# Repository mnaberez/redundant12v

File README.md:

# Rackmount Redundant 12V Power Supply

This is a redundant, but not hot-swappable, 12VDC power supply.  It has these features:

 - Two AC cords.  Either cord can lose AC power without disrupting the 12VDC output.

 - Five 12VDC output jacks.  Any individual jack can supply ~6A maximum but the supply is only capable of providing ~16A maximum across all jacks.

 - Remote monitoring.  A serial port provides a simple "on/off" status that indicates when one of the two onboard DC supplies loses its AC power or otherwise fails.

It is built on a 1U rack shelf but requires at least 2U because it is slightly taller than 1U.  The extra air space is also needed for cooling because the supply has no fans.

## Background

Rackmount [Automatic Transfer Switches](https://web.archive.org/web/20220408134749/https://www.youtube.com/watch?v=JSWmmY9tKrM) from companies such as [APC](https://web.archive.org/web/20220408135631if_/https://download.schneider-electric.com/files?p_File_Name=BSTY-AQNP38_R0_EN.pdf&p_Doc_Ref=SPD_BSTY-AQNP38_EN&p_enDocType=Catalog) and [CyberPower](https://web.archive.org/web/20220408140138if_/https://www.cyberpower.com/tw/en/File/GetCyberpowerFileByDocId/DS-21040002-01) can be used to provide AC power redundancy for devices with a single AC cord.  I wanted redundant power for the single-corded devices in my rack and noticed that they all ran off 12VDC power bricks.  Instead of buying an ATS unit and plugging the bricks into it, I built this redundant 12VDC supply to eliminate the bricks.  It can be built for less than the cost of most ATS units.

## Parts List

| Part | Qty | Notes |
|------|-----|-------|
|[Meanwell ERDN40-12 12VDC Redundancy Module](https://www.mouser.com/ProductDetail/709-ERDN40-12) | 1 | [Datasheet](https://web.archive.org/web/20220407021145if_/https://www.meanwell.com/upload/pdf/ERDN40/ERDN40-spec.pdf) |
|[Meanwell MSP-200-12 12VDC 16.7A Power Supply](https://www.mouser.com/ProductDetail/709-MSP200-12) | 2 | [Datasheet](https://web.archive.org/web/20220407021309if_/https://www.mouser.com/datasheet/2/260/MSP_200_SPEC-1109886.pdf).  Selected for built-in protections and no required minimum current. |
|[Pinfox 10' 18 AWG 3 Prong Heavy Duty 120V 10A AC Cord](https://www.amazon.com/gp/product/B07QYRMD6D) | 2 | One AC cord for each MSP-200-12. |
|[Raising Electronics 701401004 19" 1U 12" Deep Rack Shelf](https://www.amazon.com/gp/product/B01M8HKRA7) | 1 | [Product Page](https://web.archive.org/web/20220408132026if_/https://risingracks.com/cantilever-server-shelf-vented-black-shelves-rack-mount-19-1u-12-300mm-deep/) |
|[10pc M3x6mm Plastic Pan Head Screw](https://www.ebay.com/itm/254913074827) | 1 | 10 screws used for mounting the Meanwell units to the shelf.  Plastic ensures no possibility of shorting. |
|[10pc M3x25mm Female-Female Steel Standoff](https://www.ebay.com/itm/113410581076) | 1 | 4 standoffs used inside the project box to mount it to the shelf and secure the lid |
|[25pc M3x8mm Pan Head Screw Steel Black](https://www.ebay.com/itm/111839544046) | 1 | 8 screws used with the 4 project box standoffs (2 screws per standoff) |
|[50pcs M3x6mm Nylon Standoffs with M3x6mm Nylon Screws](https://www.ebay.com/itm/262850128455) | 1 | 4 standoffs and 4 screws used to mount PCB inside project box.  Plastic ensures no possibility of shorting.  Standoffs are epoxied to the project box. |
|[Hammond 1591HSBK Project Box](https://www.digikey.com/en/products/detail/hammond-manufacturing/1591HSBK/130882) | 1 | [Datasheet](https://web.archive.org/web/20210928162934if_/http://www.hammondmfg.com/pdf/1591H.pdf), [Bulletin](https://web.archive.org/web/20220407164638if_/https://www.mouser.com/datasheet/2/177/1591-1389824.pdf) |
|[L-Com SDG400XS D-Sub 50pc Jackscrew/Washer/Nut](https://www.newark.com/l-com/sdg400xs/jack-screw-4-40-10-16mm/dp/63K2685) | 1 | [Datasheet](https://web.archive.org/web/20220827230745if_/https://www.l-com.com/Images/Downloadables/2D/SDG450XS_2D.pdf).  2 jackscrews, 2 lock washers, and 2 hex nuts used to mount DB9 to project box. |
|[5pcs DB9 Female to IDC Panel Mount](https://www.ebay.com/itm/311374355272) | 1 | 1 DB9 connector used to make the DB9-to-PCB cable inside the project box. |
|[10pcs 2x5 pin IDC Female](https://www.ebay.com/itm/323745402692) | 1 | 1 IDC connector used to make the DB9-to-PCB cable inside the project box.  The top of the strain relief must be shaved down a bit to fit in the box. |
|[Ribbon Cable 14 conductor 6' long](https://www.ebay.com/itm/282211468932) | 1 | Cut down to 10 conductors and 6" long, used to make the DB9-to-PCB cable inside the project box. |
|[DB9 Male/Female 5' Cable](https://www.mouser.com/ProductDetail/523-CS-DSDMDB09MF005) | 1 | [Datasheet](https://web.archive.org/web/20220719155819if_/https://www.mouser.com/datasheet/2/18/1/CS_DSDMDB09MF-2079775.pdf).  For direct connection between the box and a PC with a DB9 serial port. |
|[FTDI-US232R-100 1m USB-Serial Cable](https://www.mouser.com/ProductDetail/895-US232R-100-BLK) | 1 | [Datasheet](https://web.archive.org/web/20220828230546if_/https://www.mouser.com/datasheet/2/163/DS_US232R-10_R-100-500-1669828.pdf).  For connecting to a PC without a DB9 serial port, use this adapter together with the above DB9 cable. |
|[Lumex SSI-LXH387GD Panel Mount Green LED](https://www.mouser.com/ProductDetail/696-SSI-LXH387GD) | 2 | [Datasheet](https://web.archive.org/web/20221002231549if_/https://www.mouser.com/datasheet/2/244/LUMX_S_A0001762456_1-2551886.pdf).  Mounted on project box to show the "on" status of each power supply.
|[Switchcraft L712ASH 2.5mm Locking Barrel Socket](https://www.mouser.com/ProductDetail/502-L712ASH) | 5 | [Datasheet](https://web.archive.org/web/20220407035419if_/https://www.mouser.com/datasheet/2/393/L712ASH-L722ASH_CD-1110860.pdf), [Bulletin](https://web.archive.org/web/20220407164041if_/https://www.switchcraft.com/Documents/switchcraft_npb_637_high_temp_jacks_plugs.pdf).  Mounted on project box for DC outputs. |
|[Switchcraft 761KSH15 2.5mm Locking Barrel Plug](https://www.mouser.com/ProductDetail/502-761KSH15) | 5 | [Datasheet](https://web.archive.org/web/20220407035117if_/https://www.mouser.com/datasheet/2/393/761KSH-S761KSH_CD-1110850.pdf). See bulletin above for electrical info.  For building DC cables out to devices. |
|[14 AWG GXL Wire 10' Long](https://www.ebay.com/itm/293094627307) | 3 | 1 each: red, green, black.  Cut to length for high current DC wiring |
|[1200Pcs Assorted Crimp Terminals](https://www.ebay.com/itm/172856488315) | 1 | 21 M4 size ring connectors used with terminal blocks on Meanwell units |
|[DC Extension Cable 18 AWG 12VDC 10A 33' Long](https://www.ebay.com/itm/133233779533) | 1 | Connectors cut off and discarded; used to make output cables and for wiring inside Project Box |
|[10pc Dupont 2x2 Female Housing](https://www.ebay.com/itm/141510327734) | 1 | 1 housing used to make ERDN40 alarm cable |
|[10pc Dupont 2-pin 26AWG Female-Female Jumper Cable](https://www.ebay.com/itm/254959908608) | 1 | 2 cables used to make ERDN40 alarm cable |
|[Molex KK 22-01-3077 7-pin Housing](https://www.mouser.com/ProductDetail/538-22-01-3077)| 1 | 1 housing used for PCB connector |
|[125pc Rubber Grommet Set](https://www.ebay.com/itm/221291687081) | 1 | 1 grommet used around wiring from ERDN40 into project box |
|[TICONN 80pc Stainless Steel Hose Clamp Set](https://www.amazon.com/gp/product/B094YP2F3D) | 1 | 3 hose clamps used for AC cord strain relief |
|[100pc 1/4" Aluminum Pop Rivet Set](https://www.harborfreight.com/100-piece-1-4-quarter-inch-aluminum-blind-rivet-set-67619.html) | 1 | 3 pop rivets used to secure hose clamps to shelf |
|[6pc Phoenix Contact Cable Tie Mount Base](https://www.mouser.com/ProductDetail/651-3240709) | 1 | 3 bases used for cable management |
|[Panduit Cable Tie Assortment](https://www.mouser.com/ProductDetail/644-KB-550) | 1 | 3 ties used for cable management |
|[42pc Marine Heat Shrink Tubing](https://www.harborfreight.com/42-piece-marine-heat-shrink-tubing-67598.html) | 1 | For insulating cable ends and also cable management |

## PCB Components

| Part | Qty | Reference Designators |
|------|-----|-----------------------|
|[ATTINY212-SSF](https://www.mouser.com/ProductDetail/579-ATTINY212-SSF) Microcontroller SOIC-8 | 1 | U1 |
|[MAX232EID](https://www.mouser.com/ProductDetail/595-MAX232EID) TI RS232 Transceiver SOIC-8 | 1 | U2 |
|[ECS-3951M-018-AU-TR](https://www.mouser.com/ProductDetail/520-3951M-018-AU) Oscillator 1.8432 MHz | 1 | X1 |
|[BZX84-A15,215](https://www.mouser.com/ProductDetail/771-BZX84-A15,215) Zener Diode 15V | 1 | D1 |
|[F1206B1R00FSTR](https://www.mouser.com/ProductDetail/581-F1206B1R00FSTR) Fuse 1206 | 1 | F1 |
|[08055C104J4T2A](https://www.mouser.com/ProductDetail/581-08055C104J4T2A) Capacitor 0.1uF 50V 0805 | 4 | C1, C2, C4, C8 |
|[08053C105K4Z4A](https://www.mouser.com/ProductDetail/581-08053C105K4Z4A) Capacitor 1uF 25V 0805 | 4 | C3, C5, C6, C7 |
|[CGA4J1X7S1E106K125AC](https://www.mouser.com/ProductDetail/810-CGA4J1X7S1E106K1) Capacitor 10uF 25V 0805 | 1 | C9 |
|[RK73H2ARTTD4702F](https://www.mouser.com/ProductDetail/660-RK73H2ARTTD4702F) Resistor 47K 0805 | 2 | R1, R2 |
|[ERJ-P06F2000V](https://www.mouser.com/ProductDetail/667-ERJ-P06F2000V) Resistor 200ohm  0805 | 2 | R3, R4 |
|[22-12-2074](https://www.mouser.com/ProductDetail/538-22-12-2074) Molex KK 7-pin Right Angle | 1 | J1 |
|[IDC 2x5 Header](https://www.ebay.com/itm/254517739367) Shrouded Through Hole | 1 | J2 |

## Author

[Mike Naberezny](https://github.com/mnaberez)

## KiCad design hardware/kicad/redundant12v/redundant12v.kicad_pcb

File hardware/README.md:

# Hardware

The redundant power supply is mostly wired by hand but a printed circuit board with a microcontroller is used to report the status to a PC.  The board was designed using KiCad.  The [schematic](./redundant12v/schematic.pdf) and [Gerber files](./redundant12v/gerbers.zip) are the final version.  See [`firmware/`](../firmware) for how to program the microcontroller.

## Photos

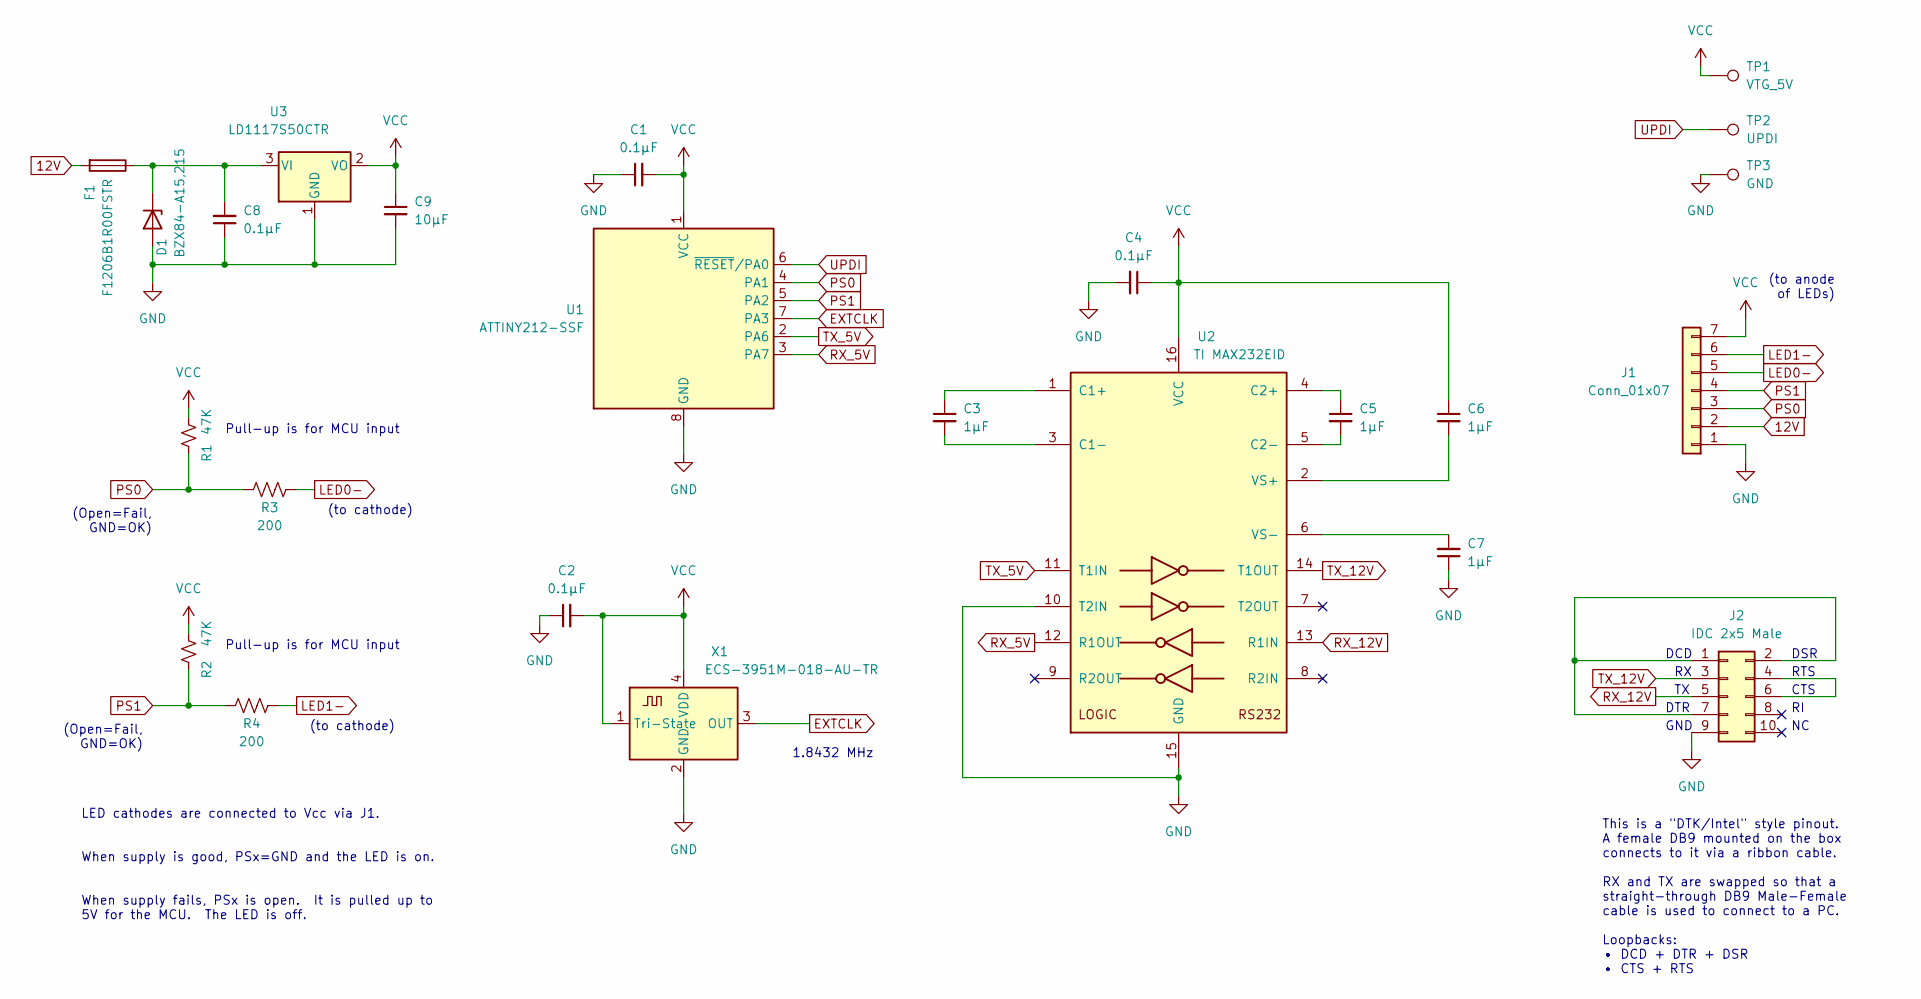
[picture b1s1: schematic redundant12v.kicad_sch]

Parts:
C1, C2, C4, C8: 0.1μF; C_0805_2012Metric_Pad1.18x1.45mm_HandSolder
C3, C5, C6, C7: 1μF; C_0805_2012Metric_Pad1.18x1.45mm_HandSolder
C9: 10μF; C_0805_2012Metric_Pad1.18x1.45mm_HandSolder
D1: BZX84-A15,215; SOT-23
F1: F1206B1R00FSTR; Fuse_1206_3216Metric_Pad1.42x1.75mm_HandSolder
J1: Conn_01x07; Molex_KK-254_AE-6410-07A_1x07_P2.54mm_Vertical
J2: IDC 2x5 Male; IDC-Header_2x05_P2.54mm_Vertical
R1, R2: 47K; R_0805_2012Metric_Pad1.20x1.40mm_HandSolder
R3, R4: 200; R_0805_2012Metric_Pad1.20x1.40mm_HandSolder
TP1: VTG_5V; TestPoint_Pad_D2.5mm
TP2: UPDI; TestPoint_Pad_D2.5mm
TP3: GND; TestPoint_Pad_D2.5mm
U1: ATTINY212-SSF; SOIC-8_3.9x4.9mm_P1.27mm
U2: TI MAX232EID; SOIC-16_3.9x9.9mm_P1.27mm
U3: LD1117S50CTR; SOT-223-3_TabPin2
X1: ECS-3951M-018-AU-TR; Oscillator_SMD_Abracon_ASV-4Pin_7.0x5.1mm_HandSoldering

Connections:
12V: F1.2, J1.2
EXTCLK: U1.7 (PA3), X1.3 (OUT)
GND: C1.1, C2.1, C4.2, C7.1, C8.1, C9.2, D1.1 (A), J1.1, J2.9, TP3.1, U1.8 (GND), U2.10 (T2IN), U2.15 (GND), U3.1 (GND), X1.2 (GND)
LED0-: J1.5, R3.2
LED1-: J1.6, R4.2
unnamed: C3.1, U2.1 (C1+)
unnamed: C3.2, U2.3 (C1-)
unnamed: C5.1, U2.4 (C2+)
unnamed: C5.2, U2.5 (C2-)
unnamed: C6.2, U2.2 (VS+)
unnamed: C7.2, U2.6 (VS-)
unnamed: C8.2, D1.3 (K), F1.1, U3.3 (VI)
unnamed: J2.1, J2.2, J2.7
unnamed: J2.4, J2.6
PS0: J1.3, R1.2, R3.1, U1.4 (PA1)
PS1: J1.4, R2.2, R4.1, U1.5 (PA2)
RX_5V: U1.3 (PA7), U2.12 (R1OUT)
RX_12V: J2.5, U2.13 (R1IN)
TX_5V: U1.2 (PA6), U2.11 (T1IN)
TX_12V: J2.3, U2.14 (T1OUT)
UPDI: TP2.1, U1.6 (~RESET/PA0)
VCC: C1.2, C2.2, C4.1, C6.1, C9.1, J1.7, R1.1, R2.1, TP1.1, U1.1 (VCC), U2.16 (VCC), U3.2 (VO), X1.1 (Tri-State), X1.4 (VDD)

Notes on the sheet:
RTS
1.8432 MHz
DTR
(to anode of LEDs)
DCD
(to cathode)
(Open=Fail, GND=OK)
LED cathodes are connected to Vcc via J1. When supply is good, PSx=GND and the LED is on. When supply fails, PSx is open. It is pulled up to 5V for the MCU. The LED is off.
This is a "DTK/Intel" style pinout. A female DB9 mounted on the box connects to it via a ribbon cable. RX and TX are swapped so that a straight-through DB9 Male-Female cable is used to connect to a PC. Loopbacks: • DCD + DTR + DSR • CTS + RTS
DSR
CTS
Pull-up is for MCU input
GND

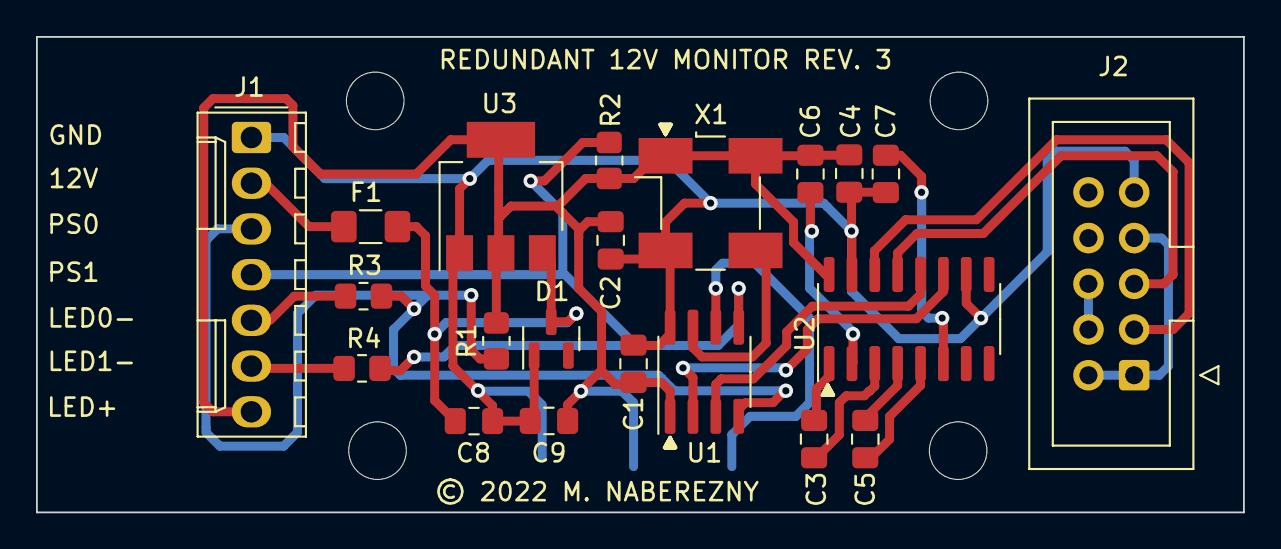
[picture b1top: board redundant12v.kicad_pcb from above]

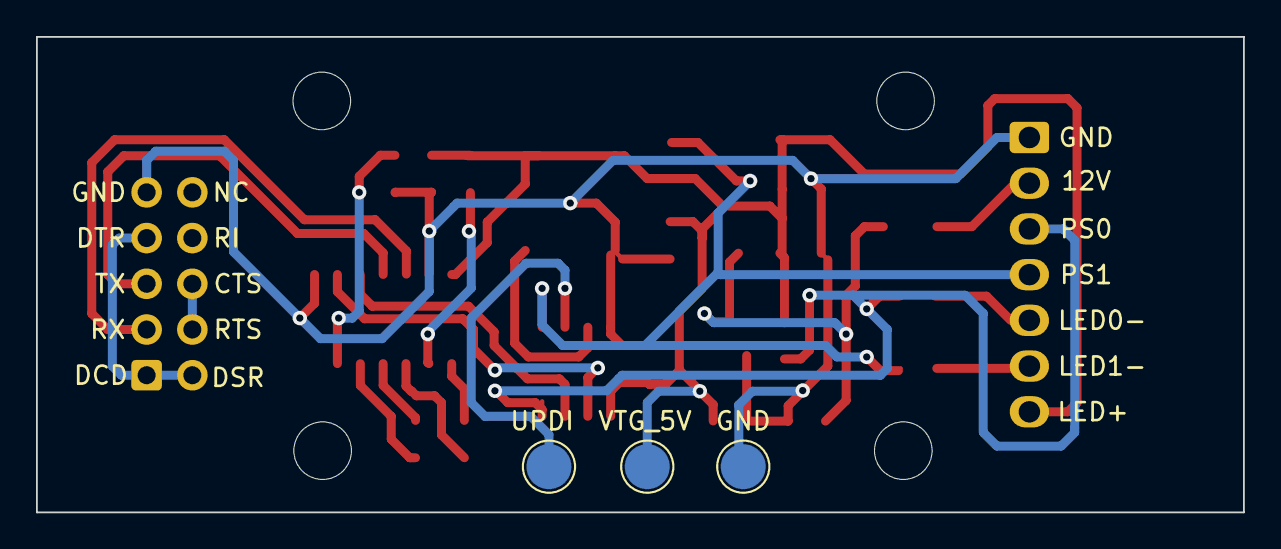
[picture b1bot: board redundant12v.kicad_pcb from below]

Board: 2 copper layers, 67.1 x 26.4 mm, 24 parts (3 on the bottom side), 22 nets.

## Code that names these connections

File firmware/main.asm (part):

;ATtiny212 or ATtiny412
;1 VCC
;2 PA6 TX to MAX232
;3 PA7 RX from MAX232
;4 PA1 Digital Input: Power Supply 0 failed (0=ok, 1=failed)
;5 PA2 Digital Input: Power Supply 1 failed (0=ok, 1=failed)
;6 UPDI
;7 EXTCLK (from 1.8432 MHz oscillator)
;8 GND
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    ldi r18, 25             ;Debounce: PORTA must be the same for N readings

1$: lds r16, PORTA_IN       ;Read once
    andi r16, 0b00000110    ;PA2=Power Supply 1, PA1=Power Supply 0

    push r16
    rcall delay_1ms         ;Delay 1ms
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
;Set up GPIO directions (UART pin directions are set in uart_init)
gpio_init:
    ldi r16, 1<<2 | 1<<1    ;PA2, PA1 = input
    sts PORTA_DIRCLR, r16
    ret

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    sts USART0_CTRLC, r16

    ;Set pin directions
    ldi r16, 1<<7           ;pa7 = rx (input)
    sts PORTA_DIRCLR, r16
    ldi r16, 1<<6           ;pa6 = tx (output)
    sts PORTA_DIRSET, r16

    ;Enable transmit and receive
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
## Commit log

2022-04-08 Initial import
2022-04-10 Add Dupot connectors to parts list
2022-06-28 Add M3 standoffs
2022-06-30 Ignore build artifacts
2022-06-30 Add initial firmware (serial loopback only)
2022-06-30 Add workflow for GitHub Actions
2022-06-30 Add license (BSD 3-clause)
2022-06-30 Add screws used with standoffs
2022-07-04 Send "PS0=OK,PS1=OK\r\n"
2022-07-04 Check both supplies at once
2022-07-04 Read power supply status pins
2022-07-05 Invert polarity of power supply input pins
2022-07-05 Ignore KiCad temporary files
2022-07-05 Start schematic in KiCad
2022-07-08 Improve debounce
2022-07-08 Add UART error handling
2022-07-08 Expand macros in listing output
2022-07-10 Add print string routine
2022-07-11 Store supply statuses as a bitfield
2022-07-11 Add ROM checksum
2022-07-11 Remove debug code that prints a number in hex out the UART
2022-07-11 Save build output as "redundant12v"
2022-07-12 Clear RAM on reset and add RAM test
2022-07-12 Use ASAVR high/low byte operators
2022-07-12 Clean up introduction in README
2022-07-12 Remove leftovers from UART app note
2022-07-13 Fill unused space with a NOP seld to reset
2022-07-13 Remove pagination, show wide symbols in listing
2022-07-13 Fatal error causes programmed reset
2022-07-13 Programmed reset on UART error
2022-07-13 Use CRCSCAN peripheral to check flash integrity
2022-07-14 Add watchdog to reset every 4 seconds
2022-07-14 Verify RAM cleared successfully
2022-07-14 Use "out" instead of "sts" where possible
2022-07-14 Use "tst" to check for zero
2022-07-14 Add fuse programming
2022-07-14 Specify file format for avrdude explicitly
2022-07-14 Specify explicit erase for avrdude
2022-07-15 Start watchdog in fuses
2022-07-15 Save two program words in RXCIF check
2022-07-15 Add firmware README
2022-07-15 Use dedicated set/clear instead of RMW
2022-07-15 Return status instead of using global
2022-07-18 Add regulator circuit and LED drivers
2022-07-18 Reorganize schematic, fix LED polarity
2022-07-19 Add DB9 parts
2022-07-19 Add serial port connections
2022-08-20 PCB is mostly routed
2022-08-21 PCB rev 1 finished
2022-08-23 Add values to components on schematic
2022-08-23 Add PCB components list
2022-08-27 Replace Maxim MAX232ECWE+T with TI MAX232EID for narrower SOIC-16
2022-08-27 Project box no longer stocked by Mouser
2022-08-27 Use L-Com SDG400XS jackscrew for mounting DB9
2022-08-27 Fix Mouser links to PCB components
2022-08-29 Add optional FTDI cable part number
2022-08-30 Add link to Hammond case mechanical drawing
2022-08-30 Add front panel drill template
2022-09-04 Add DB9 cutout to drill template
2022-09-04 Add support for Attiny412
2022-09-06 Fix alarm detection, rotate serial connector
2022-09-06 Update parts list for PCB rev 2
2022-09-19 Fix swapped anode and cathode labels
2022-09-20 Invert status logic for Rev 2 circuit change
2022-09-20 Fix typo
2022-09-22 Increase width of all traces, widen board under Molex connector
2022-10-02 Add standoffs and screws for PCB mounting
2022-10-02 Add panel mount LEDs
2022-10-02 Resistors R1, R2 are now 47K
2022-10-03 Add Gerber files
2022-10-03 Add schematic in PDF format
2022-10-03 Add UPDI connection info
2022-10-04 Replace premade cable with parts to make a shorter one
2022-10-04 Fix values of R3 and R4 on schematic
2022-10-29 Upgrade GitHub Actions steps to fix deprecation warnings
2022-10-30 Show how to include DEFSFILE in the listing output
2022-11-23 Link directly to PDF files
2022-11-26 Add photo for README
2022-11-26 Add PCB photo
2022-11-27 Add more photos and a hardware README
2022-12-05 Rename 'drill_template' to 'drill_template_panel'
2022-12-07 Add crimp connectors to parts list
2023-04-30 Ignore KiCad preferences file
2023-06-28 Upgrade files to KiCad 7
2023-06-28 Split KiCad projects into subdirectories
2023-10-13 Build using ASxxxx 5.50
2023-10-21 Fix typos in comments

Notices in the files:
hardware/kicad/redundant12v/redundant12v.kicad_pcb:
© 2022 M. NABEREZNY
